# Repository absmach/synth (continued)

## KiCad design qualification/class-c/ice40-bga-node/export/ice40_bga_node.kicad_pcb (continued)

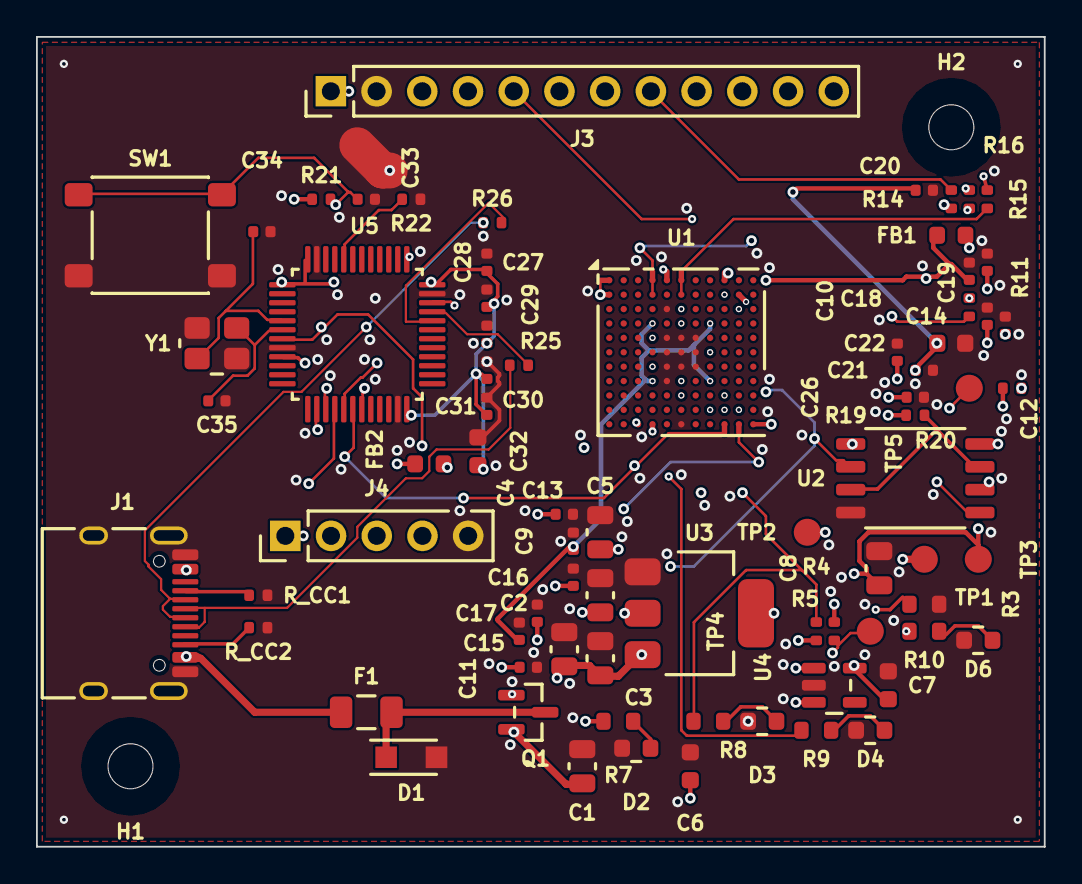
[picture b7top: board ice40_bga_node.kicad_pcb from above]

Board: 6 copper layers, 56.0 x 45.0 mm, 77 parts (0 on the bottom side), 42 nets.

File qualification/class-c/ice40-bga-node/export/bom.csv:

refdes,value,kind,description,kicad_symbol,kicad_footprint,lcsc_pn,mpn
C1,10uF,capacitor,"Generic 0805 MLCC, X7R/X5R, any value",Device:C,Capacitor_SMD:C_0805_2012Metric,,
C10,100nF,capacitor,"Generic 0402 MLCC, X7R/X5R, any value",Device:C,Capacitor_SMD:C_0402_1005Metric,,
C11,100nF,capacitor,"Generic 0402 MLCC, X7R/X5R, any value",Device:C,Capacitor_SMD:C_0402_1005Metric,,
C12,100nF,capacitor,"Generic 0402 MLCC, X7R/X5R, any value",Device:C,Capacitor_SMD:C_0402_1005Metric,,
C13,100nF,capacitor,"Generic 0402 MLCC, X7R/X5R, any value",Device:C,Capacitor_SMD:C_0402_1005Metric,,
C14,100nF,capacitor,"Generic 0402 MLCC, X7R/X5R, any value",Device:C,Capacitor_SMD:C_0402_1005Metric,,
C15,100nF,capacitor,"Generic 0402 MLCC, X7R/X5R, any value",Device:C,Capacitor_SMD:C_0402_1005Metric,,
C16,100nF,capacitor,"Generic 0402 MLCC, X7R/X5R, any value",Device:C,Capacitor_SMD:C_0402_1005Metric,,
C17,100nF,capacitor,"Generic 0402 MLCC, X7R/X5R, any value",Device:C,Capacitor_SMD:C_0402_1005Metric,,
C18,100nF,capacitor,"Generic 0402 MLCC, X7R/X5R, any value",Device:C,Capacitor_SMD:C_0402_1005Metric,,
C19,100nF,capacitor,"Generic 0402 MLCC, X7R/X5R, any value",Device:C,Capacitor_SMD:C_0402_1005Metric,,
C2,10uF,capacitor,"Generic 0805 MLCC, X7R/X5R, any value",Device:C,Capacitor_SMD:C_0805_2012Metric,,
C20,100nF,capacitor,"Generic 0402 MLCC, X7R/X5R, any value",Device:C,Capacitor_SMD:C_0402_1005Metric,,
C21,100nF,capacitor,"Generic 0402 MLCC, X7R/X5R, any value",Device:C,Capacitor_SMD:C_0402_1005Metric,,
C22,1uF,capacitor,"Generic 0603 MLCC, X7R/X5R, any value",Device:C,Capacitor_SMD:C_0603_1608Metric,,
C26,100nF,capacitor,"Generic 0402 MLCC, X7R/X5R, any value",Device:C,Capacitor_SMD:C_0402_1005Metric,,
C3,10uF,capacitor,"Generic 0805 MLCC, X7R/X5R, any value",Device:C,Capacitor_SMD:C_0805_2012Metric,,
C4,10uF,capacitor,"Generic 0805 MLCC, X7R/X5R, any value",Device:C,Capacitor_SMD:C_0805_2012Metric,,
C5,10uF,capacitor,"Generic 0805 MLCC, X7R/X5R, any value",Device:C,Capacitor_SMD:C_0805_2012Metric,,
C6,1uF,capacitor,"Generic 0603 MLCC, X7R/X5R, any value",Device:C,Capacitor_SMD:C_0603_1608Metric,,
C7,1uF,capacitor,"Generic 0603 MLCC, X7R/X5R, any value",Device:C,Capacitor_SMD:C_0603_1608Metric,,
C8,4.7uF,capacitor,"Generic 0805 MLCC, X7R/X5R, any value",Device:C,Capacitor_SMD:C_0805_2012Metric,,
C9,100nF,capacitor,"Generic 0402 MLCC, X7R/X5R, any value",Device:C,Capacitor_SMD:C_0402_1005Metric,,
D1,PTVS6V0S1UR,diode,"Nexperia PTVS6V0S1UR 400 W unidirectional TVS, 6.0 V standoff, SOD123W, for VBUS and CC",Device:D_Zener,Diode_SMD:Nexperia_CFP3_SOD-123W,,PTVS6V0S1UR
D2,0603-GREEN,led,"Green LED, 0603 package, ~2.2V Vf",Device:LED,LED_SMD:LED_0603_1608Metric,C72043,0603-GREEN
D3,(no value),led,"Amber surface-mount LED, 0603",Device:LED,LED_SMD:LED_0603_1608Metric,,
D4,0603-RED,led,"Red LED, 0603 package, ~2.0V Vf",Device:LED,LED_SMD:LED_0603_1608Metric,C2286,0603-RED
D6,0603-RED,led,"Red LED, 0603 package, ~2.0V Vf",Device:LED,LED_SMD:LED_0603_1608Metric,C2286,0603-RED
F1,MF-NSMF050-2,fuse,"Bourns MF-NSMF050-2 resettable fuse, 0.5 A hold, 13.2 V, 1206",Device:Polyfuse,Fuse:Fuse_1206_3216Metric,C75464,MF-NSMF050-2
FB1,(no value),inductor,"0603 ferrite bead, 600Ω @ 100MHz — EMI suppression",Device:FerriteBead,Inductor_SMD:L_0603_1608Metric,,
H1,(no value),mounting_hole,M2.5 non-plated mounting hole (NPTH) for a board corner,Mechanical:MountingHole,MountingHole:MountingHole_2.5mm,,
H2,(no value),mounting_hole,M2.5 non-plated mounting hole (NPTH) for a board corner,Mechanical:MountingHole,MountingHole:MountingHole_2.5mm,,
J1,HX PZ2.54-1x2P ZZ,connector,"1x2 through-hole pin header, 2.54mm pitch, for a jumper",Connector_Generic:Conn_01x02,Connector_PinHeader_2.54mm:PinHeader_1x02_P2.54mm_Vertical,C32713268,HX PZ2.54-1x2P ZZ
J3,(no value),connector,"1x12 through-hole pin header, 2.54 mm pitch (GPIO); datasheet_url is the product page of the Harwin M20 series, no manufacturer PDF link was verifiable",Connector_Generic:Conn_01x12,Connector_PinHeader_2.54mm:PinHeader_1x12_P2.54mm_Vertical,,
Q1,SI2301CDS-T1-GE3,transistor,"Vishay Si2301 P-channel power MOSFET, SOT-23",Transistor_FET:Si2301CDS,Package_TO_SOT_SMD:SOT-23,C10487,SI2301CDS-T1-GE3
R10,1k,resistor,"Generic 0603 thick-film resistor, any value",Device:R_US,Resistor_SMD:R_0603_1608Metric,,
R11,100,resistor,"Generic 0402 thick-film resistor, any value",Device:R_US,Resistor_SMD:R_0402_1005Metric,,
R14,100,resistor,"Generic 0402 thick-film resistor, any value",Device:R_US,Resistor_SMD:R_0402_1005Metric,,
R15,100,resistor,"Generic 0402 thick-film resistor, any value",Device:R_US,Resistor_SMD:R_0402_1005Metric,,
R16,100,resistor,"Generic 0402 thick-film resistor, any value",Device:R_US,Resistor_SMD:R_0402_1005Metric,,
R19,10k,resistor,"Generic 0402 thick-film resistor, any value",Device:R_US,Resistor_SMD:R_0402_1005Metric,,
R20,10k,resistor,"Generic 0402 thick-film resistor, any value",Device:R_US,Resistor_SMD:R_0402_1005Metric,,
R3,100k,resistor,"Generic 0603 thick-film resistor, any value",Device:R_US,Resistor_SMD:R_0603_1608Metric,,
R4,10k,resistor,"Generic 0402 thick-film resistor, any value",Device:R_US,Resistor_SMD:R_0402_1005Metric,,
R5,10k,resistor,"Generic 0402 thick-film resistor, any value",Device:R_US,Resistor_SMD:R_0402_1005Metric,,
R7,1k,resistor,"Generic 0603 thick-film resistor, any value",Device:R_US,Resistor_SMD:R_0603_1608Metric,,
R8,1k,resistor,"Generic 0603 thick-film resistor, any value",Device:R_US,Resistor_SMD:R_0603_1608Metric,,
R9,1k,resistor,"Generic 0603 thick-film resistor, any value",Device:R_US,Resistor_SMD:R_0603_1608Metric,,
TP1,(no value),testpoint,"SMD test point pad, 1.5 mm — probe point for a net",Connector:TestPoint,TestPoint:TestPoint_Pad_D1.5mm,,
TP2,(no value),testpoint,"SMD test point pad, 1.5 mm — probe point for a net",Connector:TestPoint,TestPoint:TestPoint_Pad_D1.5mm,,
TP3,(no value),testpoint,"SMD test point pad, 1.5 mm — probe point for a net",Connector:TestPoint,TestPoint:TestPoint_Pad_D1.5mm,,
TP4,(no value),testpoint,"SMD test point pad, 1.5 mm — probe point for a net",Connector:TestPoint,TestPoint:TestPoint_Pad_D1.5mm,,
TP5,(no value),testpoint,"SMD test point pad, 1.5 mm — probe point for a net",Connector:TestPoint,TestPoint:TestPoint_Pad_D1.5mm,,
U1,ICE40HX4K-BG121,fpga,"Lattice iCE40 HX4K FPGA, 121-ball 0.8mm BGA. Copy of registry part ice40hx4k_bg121 with exactly one change: vpp_fast (B10) is a passive pin that is not required, so it can be left unconnected.",FPGA_Lattice:ICE40HX4K-BG121,Package_BGA:BGA-121_9.0x9.0mm_Layout11x11_P0.8mm_Ball0.4mm_Pad0.35mm_NSMD,,ICE40HX4K-BG121
U2,W25Q128JVSIQ,memory,"Winbond W25Q128JVSIQ 128Mbit SPI NOR flash, SOIC-8 208 mil (5.3 mm body, 7.7 mm lead span, 1.27 mm pitch)",Memory_Flash:W25Q128JVS,Package_SO:SOIC-8_5.3x5.3mm_P1.27mm,C97521,W25Q128JVSIQ
U3,AMS1117-3.3,regulator,"AMS1117-3.3 fixed 3.3V LDO regulator, SOT-223 — common JLC stock",Regulator_Linear:AMS1117-3.3,Package_TO_SOT_SMD:SOT-223-3_TabPin2,C6186,AMS1117-3.3
U4,TLV70012-1.2,regulator,"TI TLV70012 1.2 V fixed LDO, 200 mA, 2.0 to 5.5 V input, SOT-23-THIN (DDC, TSOT-23-5). Pinout 1 IN, 2 GND, 3 EN, 4 NC, 5 OUT per TI TLV700xx datasheet SLVSA00; 1 uF input and output capacitors.",Regulator_Linear:TLV70012_SOT23-5,Package_TO_SOT_SMD:TSOT-23-5,,TLV70012DDCR

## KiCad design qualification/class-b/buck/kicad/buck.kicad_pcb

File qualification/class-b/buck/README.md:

# 24 V in, 3.3 V out buck with input parts (PTC, reverse-block diode, TVS) (SYN-67)

Status: designed, placed by a hand-pinned sidecar, routed, DRC and ERC counted, Gerber and drill files
generated. Not fabricated, not powered, no hardware test. Every part on the board that carries a
registry review record is signed; the last two, `lmr38010` and `ltst_c190kgkt`, were reviewed by Steve Munene
on 2026-10-29 and their review records are below. The fab package reports `release_ready: true`, which covers
Synth's routing and export gates only, not fabrication.
Intended for 24 V +10% in and 1 A out. The converter is rated 1 A, and the PTC and the input connector are
further limits (see Limits). No surge test was run. The TVS clamp (48.4 V at 12.4 A) is below the
converter's 85 V absolute maximum; a sustained overvoltage is limited by the PTC and the 50 V capacitors.

## Purpose

Ticket #67 under #38 (Class B qualification): a switching-regulator board with input and output filtering,
feedback, power-good and thermal copper, plus a negative variant that the feedback-safety rule
(E-SYNTH-POWER-011, PR #56) must flag.

## What

- `buck.synth`, negative `buck_neg_fb_sw.synth`, the placement sidecar `buck.placement.layout.toml`, hashes in `SHA256SUMS`, matrix and `#38` traceability in `QUALIFICATION.md`, evidence in `kicad/`, `reports/`, `images/`. `kicad/buck.step` is the board STEP with 3D models (`kicad-cli pcb export step --no-dnp`); the 3D views use the same stock KiCad models. The mounting holes have no model (the KiCad MountingHole step files are not installed).
- `kicad/`: the KiCad project, BOM, pick-and-place, `gerbers/` (22 Gerbers plus the job file, 4 copper layers) and `drill/` (PTH and NPTH). `reports/`: `release.json` (source/DRC gate) and `release-fab.json` (fab package), DRC, ERC, routing and connectivity.
- Chain: J1 (JST XH) -> F1 PTC -> D1 SS36 Schottky (reverse block) -> VIN node.
  VIN node: D2 SMBJ30A TVS, C1 47 uF bulk, C2 10 uF, C3 220 nF (on the U1 VIN pin), U1 LMR38010, UVLO divider.
- U1 -> L1 6.8 uH -> C5, C6, C9 (3x 22 uF, 25 V X7R) -> J2. C4 100 nF boot. R_RT 33k from RT/SYNC to GND sets 800 kHz. U1 has no VCC pin, so there is no VCC capacitor.
- U1 pins: 1 GND, 2 EN, 3 VIN, 4 RT/SYNC, 5 FB, 6 PG, 7 BOOT, 8 SW, 9 exposed pad.
- Feedback: R_FB_T 100k from the output node (L1 pad 2 side), R_FB_B 43.2k, C7 56 pF across R_FB_T.
  Vout = 1.0 x (1 + 100k/43.2k) = 3.315 V typical, 3.26 to 3.36 V over Vref 0.985 to 1.015 V (ideal resistors).
- Power-good: U1 pin 6 is open drain, pulled up to +3V3 through R_PG 100k and brought out on J2 pin 3. D4 (green, "PG FAULT") and R_PGLED 470 R run from +3V3 to PG, so the LED lights while PG is low and stays dark while power is good.
- Thermal: U1 pin 9 is a 2.41 x 3.1 mm exposed pad soldered to the F.Cu GND pour, with a 2 x 3 array of six GND vias in the pad (see Thermal). The board is `manufacturer "jlc-filled-via"` with `requires via_in_pad` (resin-filled and capped vias).
- Negative file: identical except R_FB_T and C7 hang from SW. It emits E-SYNTH-POWER-011 and the same 11 warnings as the good board.
- Board: 70.99 x 33.99 mm (2413 mm2, Edge.Cuts line centres), 4 layers, GND pours on all layers. Power tracks 0.5 mm, signal 0.127 mm.
- Two M2.5 non-plated mounting holes (H1, H2) in opposite corners.

## Why LMR38010 and not LMR33640

The first revision used the LMR33640 (38 V absolute maximum). A review found that the SMBJ30A clamps at 48.4 V
(12.4 A), above that maximum, so the TVS could not protect it. The LMR38010 is rated 85 V absolute maximum
(SW 85 V too), above the clamp. The change also removed the VCC pin and its capacitor, moved PG to pin 6
and VIN to pin 3, and added R_RT.

## UVLO (LMR38010 SNVSBM3B, 9.2.2.8, Eq 13 and 14)

Datasheet values: VEN-H (rising) 1.1 / 1.25 / 1.4 V and VEN-L (falling) 0.95 / 1.10 / 1.22 V (min/typ/max).
R_UV_B = 100k, R_UV_T = 1.37M, ratio 1 + 13.7 = 14.7.
- Start = 1.25 x 14.7 = 18.4 V typical (16.2 to 20.6 V over the VEN-H range).
- Stop = 1.10 x 14.7 = 16.2 V typical (14.0 to 17.9 V over the VEN-L range).
- The min and max of the two ranges are not independent, so the extreme pairs are not a guaranteed hysteresis. 1% resistors add about 1% to each figure.
- EN at 28 V in is 28 x 0.1/1.47 = 1.90 V; the EN absolute maximum is VIN + 0.3 V.

## Frequency and inductor

- R_RT 33k gives 800 kHz (datasheet RT versus frequency table under Figure 8-4; Table 8-1 lists 750 kHz at 34.8k and 1000 kHz at 25.5k). The RT/SYNC pin must not float (8.3.4).
- L1 6.8 uH: ripple (26.4 - 3.3) x (3.3/26.4) / (6.8 uH x 800 kHz) = 0.53 A pp at 26.4 V in. Eq 11 minimum is 0.25 x 3.3 / 800 kHz = 1.03 uH. At 1 A out the peak is about 1.27 A against Isat 5.7 A.
- Datasheet Table 9-1 has no 3.3 V row. Its 5 V rows use 2 to 3 x 22 uF; C5, C6 and C9 are 3 x 22 uF at 25 V X7R. DC-bias derating at 3.3 V is unknown and stability is unverified.

## Power-good

| Item | Value | Source |
| --- | --- | --- |
| Pin | U1 pin 6, open-drain NMOS | SNVSBM3B 8.3.5 |
| Pull-up | R_PG 100k to +3V3 | 8.3.5 allows a 100k pull-up to VOUT; the pin tolerates 20 V (7.1, 7.3) |
| Sink current | 33 uA through 100k, limit 5 mA DC | 8.3.5 |
| On-resistance | 92 ohm typ at VEN 3.3 V, 140 ohm at VEN 0 | 7.5 |
| Asserted low | during start-up, current limit and thermal shutdown, and when EN is low | 8.3.5 |
| Thresholds | rising 110 / 112 / 114 %, falling 90 / 92 / 94 % of VFB, hysteresis 2.2 % | 7.5 |
| Start-up delay | about 4 ms from EN asserted | 8.3.5 |
| Glitch filter | 40 us typ | 7.5 |
| Presented on | J2 pin 3 (3.3 V logic) | this board |

The netlist proves the connection (A15 in `QUALIFICATION.md`). Nothing proves the thresholds, the delay or
the behaviour on a fault: Synth has no power-good rule (`synth capability list` marks
`power_sequencing_and_power_good` unsupported), and this board was not powered.

## Thermal

- U1's exposed pad (pin 9, 2.41 x 3.1 mm, centre (33.0, 16.0) mm) is soldered to the F.Cu GND pour and holds
  a 2 x 3 array of six GND vias (0.6 mm pad, 0.3 mm drill, 1.2 mm apart), declared in
  `buck.placement.layout.toml` as `[[vias]]`. The PCB export writes them before routing, so the router
  treats them as GND copper. TI asks for at least a 4 x 3 array of 10 mil vias (9.5.1.1); six vias is fewer.
- Via-in-pad needs resin-filled and capped vias, so the board declares `manufacturer "jlc-filled-via"` and
  `requires via_in_pad`; `release.json` lists the six vias as fabrication notes.
- Counts from `kicad/buck.kicad_pcb` (`vias.py`, GND vias, distance from the pad centre): inside the pad 6;
  within 1 mm 2, within 2 mm 6, within 3 mm 6, within 4 mm 7. The board has 21 vias in total, all GND, all
  0.3 mm drill and 0.6 mm pad. The other 15 were placed by the router.
- Not estimated: TI's `RthetaJA` of 42.9 C/W is not valid for design (datasheet text near Eq 15), the LMR38010
  datasheet has no copper-area curve, and no efficiency curve was read. At 1 A out and an assumed 85% efficiency the loss
  would be 3.3/0.85 - 3.3 = 0.58 W; the junction temperature is left to the expert (B2).

## Parts and datasheets (read 2026-10-24 and 2026-10-29)

| Part | Datasheet | Revision | Values taken | Conflict or gap |
| --- | --- | --- | --- | --- |
| U1 TI LMR38010SDDAR (HSOIC-8 DDA) | https://www.ti.com/lit/ds/symlink/lmr38010.pdf | SNVSBM3B | 4.2-80 V recommended, 85 V abs max (SW 85 V); 1 A; 200-2200 kHz adjustable; internal compensation; VREF 1.0 V (0.985-1.015); EN rising 1.1/1.25/1.4 V, falling 0.95/1.10/1.22 V; PG tolerates 20 V; pins 1 GND, 2 EN, 3 VIN, 4 RT/SYNC, 5 FB, 6 PG, 7 BOOT, 8 SW, 9 EP; Cin at least 4.7 uF plus 100-220 nF (9.2.2.6) | Table 8-1 has no 800 kHz row; the RT table under Figure 8-4 gives 33k. Table 9-1 has no 3.3 V row |
| L1 Bourns SRN6045TA-6R8M | https://www.bourns.com/docs/Product-Datasheets/SRN6045TA.pdf | REV. 06/24 (footer) | 6.8 uH +-20%, DCR 34 mOhm typ, Irms 3.6 A, Isat 5.7 A (L -30%), 6.0 x 6.0 mm | Registry has no Isat field; Isat is in the description |
| D1 Vishay SS36 | https://www.vishay.com/docs/88751/ss32.pdf | 23-Apr-2020 (doc 88751) | VRRM 60 V, 3 A, IFSM 100 A, VF 0.75 V max at 3 A, IR 0.5 mA at 25 C and 10 mA at 100 C, SMC | Drawn with KiCad `Device:D_Schottky`; the footprint is `Diode_SMD:D_SMC`. VF at low current not read |
| D2 Vishay SMBJ30A | https://www.vishay.com/docs/88392/smbj.pdf | 09-Jan-2024 (doc 88392) | 600 W 10/1000 us, VWM 30 V, VBR 33.3-36.8 V at 1 mA, VC 48.4 V at 12.4 A, VBR temperature coefficient 0.099 %/C, SMB | No KiCad SMBJ30A symbol; Device:D_Zener used. Registry `max_voltage_v` 30 is VWM. The clamp is below U1's 85 V absolute maximum |
| F1 Bourns MF-MSMF110/33X | https://www.bourns.com/docs/Product-Datasheets/mfmsmf.pdf | REV. BE, 09/26 (footer) | Vmax 33 V, Imax 20 A, Ihold 1.1 A at 23 C, 0.93 A at 40 C, 0.73 A at 60 C, 0.63 A at 70 C, 0.50 A at 85 C, Itrip 2.2 A, R 0.06-0.20 Ohm | none found. Registry `max_current_ma` 1100 is Ihold at 23 C |
| J1, J2 JST B2B-XH-A / B4B-XH-A | https://www.jst-mfg.com/product/pdf/eng/eXH.pdf | none printed | 2.5 mm pitch, 3 A, 250 V | Existing registry `jst_xh_2pin`/`jst_xh_4pin` say 5 V / 100 mA; that conflicts with this sheet, so new parts were added |
| D3, D4 Lite-On LTST-C190KGKT | https://optoelectronics.liteon.com/upload/download/DS22-2000-074/LTST-C190KGKT.PDF | Spec No. DS22-2000-074, Revision O, effective 09/04/2021 (read 2026-10-29) | see the review record below | none against the registry file; one footprint difference, below |
| C1 47 uF | Honor Elec RVT1H470M0810 (JLCPCB C2895739) | [LCSC datasheet](https://wmsc.lcsc.com/wmsc/upload/file/pdf/v2/lcsc/2109290630_Honor-Elec-RVT1H470M0810_C2895739.pdf) | 47 uF, 50 V, +/-20 %, 105 C, 8 x 10.2 mm SMD; ripple 120 mA at 120 Hz | ESR not given |
| C2, C5, C6, C9 (1206), C3, C4, C7, R_RT and the other resistors (0603) | none | | generic registry parts; voltage and dielectric are set per instance in `buck.synth` | no MPN. Murata and TDK pages returned 404/403/500: no DC-bias data |

### Review record: D3, D4 Lite-On LTST-C190KGKT

Read from the datasheet above on 2026-10-29. Registry file `registry/parts/diodes/ltst_c190kgkt.synth.toml`.

- Package: 1.6 x 0.8 mm body, 0.8 mm tall, 0.4 mm terminals, cathode marked on the package. Recommended pad 0.8 x 0.8 mm each, 2.3 mm outer span.
- Ratings: DC forward current 30 mA, power 75 mW, reverse voltage 5 V. Electrical: VF 1.9-2.4 V at 20 mA, IV 18-71 mcd at 20 mA, dominant wavelength 567.5-576.5 nm (green AlInGaP), IR 10 uA at 5 V.
- Registry: pin 1 cathode, pin 2 anode; `kicad_symbol` Device:LED (K=1, A=2); footprint `LED_SMD:LED_0603_1608Metric` (pad 1 cathode, pad 2 anode); `max_current_ma` 30 agrees with the DC rating; Vf 1.9 to 2.4 V in the description agrees; width 2.96 mm is the footprint courtyard width, not a datasheet figure.
- Footprint: the KiCad pads are 0.875 x 0.95 mm at +-0.7875 mm, an outer span of 2.45 mm. Datasheet: 0.8 x 0.8 mm and 2.3 mm. So the KiCad pads are 0.075 mm wider, 0.15 mm longer in Y, and the outer span is 0.15 mm larger. Polarity agrees. Pad shape differences are for the reviewer to accept.
- Circuit: D3 from +3V3 through R_LED 470 ohm: (3.3 - 2.4 to 1.9) / 470 = 1.9 to 3.0 mA, well under 30 mA. D4 likewise through R_PGLED.
- Not checked: availability, LCSC number, the Lite-On temperature derating curve against the board temperature.

Reviewed by Steve Munene on 2026-10-29; `reviewed_by` and `reviewed_at` are set in the registry file.

### Review record: U1 TI LMR38010SDDAR

Read from SNVSBM3B (text copy), 2026-10-29. Registry file `registry/parts/regulators/lmr38010.synth.toml`.

- Pins: registry gnd 1, en 2, vin 3, rt_sync 4, fb 5, pg 6, boot 7, sw 8, pad 9; the datasheet pin table agrees.
- Ratings used: operating 4.2 to 80 V (registry min 4.2, max 80, 1000 mA); absolute maximum VIN and SW 85 V, EN VIN + 0.3 V, FB and RT/SYNC 5.5 V, PG 20 V; VREF 1.0 V; junction temperature -40 to 150 C.
- Footprint: `HSOP-8-1EP_3.9x4.9mm_P1.27mm_EP2.41x3.1mm`, exposed pad 2.41 x 3.1 mm. The datasheet DDA land pattern shows a 2.40 x 3.10 mm pad. The 0.01 mm difference is below the drawing tolerance. The signal pads are 1.6 x 0.6 mm on a 1.27 mm pitch; they were not compared with the DDA drawing line by line.
- Application: Cin at least 4.7 uF plus 100-220 nF (C2 10 uF, C3 220 nF); inductor above the Eq 11 minimum (1.03 uH against 6.8 uH); PG pull-up and EN divider as in the sections above.
- Not checked: availability, LCSC number.

Reviewed by Steve Munene on 2026-10-29; `reviewed_by` and `reviewed_at` are set in the registry file.

## Limits and honesty notes

- Overvoltage: the converter is rated 80 V operating and 85 V absolute maximum. SMBJ30A has VBR 33.3 to 36.8 V
  and VC 48.4 V at 12.4 A (Vishay smbj.pdf, 600 W 10/1000 us), below the 85 V maximum, so a surge the TVS can
  absorb leaves the regulator inside its absolute maximum. A SUSTAINED overvoltage is limited by other parts:
  the PTC F1 (Vmax 33 V) and the 50 V ratings of C1, C2 and C3. No surge test was run and no IEC 61000-4-5
  rating is claimed. The TVS energy, the PTC under surge and the capacitors at the 48.4 V clamp (50 V parts,
  1.6 V margin) are for the expert (B1). The TVS standoff (30 V) is above the 26.4 V maximum input, so it
  does not conduct on a healthy rail.
- PTC and rating: output current is rated 1 A (the converter's limit). At 1 A out the input current is
  3.3 / 0.85 / 24 = 0.162 A at 24 V and 0.240 A at the UVLO stop voltage (16.2 V), against F1 Ihold 0.63 A at
  70 C (3.9x and 2.6x). The 85% efficiency is an assumption.
- Output capacitors: C5, C6 and C9 are 22 uF 25 V X7R 1206. DC-bias derating at 3.3 V is unknown. The internal
  compensation is specified for a range of inductance and capacitance; stability is unverified.
- Input capacitors: the datasheet asks for at least 4.7 uF plus 100-220 nF. C2 is 10 uF X7R 50 V; its effective
  value at 24 V is unknown. C1 47 uF electrolytic adds bulk with unknown ESR.
- Reverse polarity: Schottky chosen over a P-FET. SS36 VRRM 60 V against 26 V. Drop 0.75 V max at 3 A,
  so under 0.13 W at 0.162 A (bound; VF at low current not read). A P-FET at 24 V needs a gate clamp;
  no P-FET datasheet was read.

## Commands

```
export XDG_DATA_HOME=$(mktemp -d)   # empty dir: a user overlay in ~/.local/share/synth shadows registry parts
export KICAD_SYMBOL_DIR=/usr/share/kicad/symbols KICAD_FOOTPRINT_DIR=/usr/share/kicad/footprints
scripts/setup-routing-engines.sh --freerouting-only          # FreeRouting jar + Java, or symlink tools/freerouting and tools/jre25
B=qualification/class-b/buck                                 # relative to the repo root
synth validate $B/buck.synth
SYNTH_SOURCE_REVISION=$(git rev-parse HEAD) synth export-kicad $B/buck.synth --out out/buck \
  --allow-unverified-parts --validate-erc --router free-routing --pnp --gerbers --drill   # fab package: reports/release-fab.json
SYNTH_SOURCE_REVISION=$(git rev-parse HEAD) synth export-kicad $B/buck.synth --out out/buck-nofab \
  --allow-unverified-parts --validate-erc --router free-routing                           # source/DRC gate: reports/release.json
kicad-cli pcb drc --severity-all --refill-zones --format json -o $B/reports/buck.kicad-drc.json $B/kicad/buck.kicad_pcb
kicad-cli sch erc --severity-all --format json -o $B/reports/buck.kicad-erc.json $B/kicad/buck.kicad_sch
synth validate $B/buck_neg_fb_sw.synth
python3 -I $B/pad_gaps.py $B/kicad/buck.kicad_pcb
```

`out/` is gitignored scratch. The sidecar `buck.placement.layout.toml` decides placement; there is no
`--place-route-iterate`. The two `export-kicad` runs differ only in whether the fab gate is asked, which is why
there are two release reports. The repository root prefix was stripped from the JSON reports with `sed`.
Registry parts were authored or imported with `synth part import-kicad` and then edited by hand (names, MPN,
dimensions, datasheet URL, `switch_node` on SW and `feedback` on FB); `lmr38010` is hand-written from the
datasheet.

## Measured results

The export routes with FreeRouting 2.4.1 on OpenJDK 25.0.4.1; the routed board is written as `out/buck/buck.kicad_pcb` when Synth's gate passes (state `routed`). Numbers below are from the committed files, measured 2026-10-29. `reports/buck.routing.json` records `source_revision` a9c7546e4aeecee7719aa003f3699064bb30b912, the commit of the sources the board was built from.

| Number | Value | Command |
| --- | --- | --- |
| validate, good board | exit 0, 0 errors, 11 warnings (3 E-SYNTH-SCHEM-003, 1 E-SYNTH-SCHEM-004, 4 E-SYNTH-SCHEM-005, 1 W-SYNTH-ANOMALY-001, 2 W-SYNTH-SUPPLY-002) | `synth validate $B/buck.synth 2>&1 \| grep -o '^warning: \[[A-Z0-9-]*\]' \| sort \| uniq -c` |
| validate, negative | exit 1, 1 error (E-SYNTH-POWER-011), the same 11 warnings | same on `buck_neg_fb_sw.synth` |
| routing | `routed`, 13 nets connected, 0 open, 97 segments (all F.Cu), 21 vias, 200.08 mm | `reports/buck.routing.json` `statistics`; the PCB file also holds 97 segments and 21 vias |
| Synth routing check | kicad_drc 0 errors, 0 unconnected, 0 warnings | `reports/buck.routing.json` `validation` |
| Release gate | `release_ready` true, `production_status` production, 0 signal-integrity findings (0 `W-SYNTH-DRC-016`); with `--gerbers --drill` the same board also reports `release_ready` true and `production`, and its `reviewer_state` lists `lmr38010` and `ltst_c190kgkt` as reviewed (Steve Munene, 2026-10-29) | `reports/release.json`, `reports/release-fab.json` |
| DRC | 0 errors, 0 unconnected, 0 warnings | `kicad-cli pcb drc ... -o reports/buck.kicad-drc.json` |
| ERC | 0 violations | `kicad-cli sch erc ... -o reports/buck.kicad-erc.json` |
| Schematic netlist | 13 nets: the source's 7 `net` blocks plus the 6 further names its 10 `connect` statements create (`+3V3` joins an existing net), node for node | `kicad-cli sch export netlist --format kicadsexpr -o /tmp/buck.net $B/kicad/buck.kicad_sch` |
| Outline | 70.99 x 33.99 mm (x 0.55 to 71.54, y 0.55 to 34.54), 2413 mm2 | `grep -A3 gr_line $B/kicad/buck.kicad_pcb \| grep -E 'start\|end'` |
| Manufacturing exports | 22 Gerbers plus the job file (4 copper layers), PTH 27 holes (21 x 0.3 mm vias, 4 x 0.95 mm and 2 x 1.0 mm connector pins), NPTH 2 x 2.5 mm mounting holes | `ls $B/kicad/gerbers $B/kicad/drill`; `grep -c '^X' $B/kicad/drill/buck-PTH.drl` |
| Hashes | full values in `SHA256SUMS` and `QUALIFICATION.md` | `cd $B && grep -v '^#' SHA256SUMS \| sha256sum -c -` |

Pad-edge gaps in the placed, routed board, from `pad_gaps.py` (pcbnew pad bounding boxes, edge to edge):

| Pair | Gap mm |
| --- | --- |
| C3 (220 nF) to U1 VIN | 0.82 |
| C2 (10 uF) to U1 VIN | 1.46 |
| C3 / C2 ground pad to U1 GND | 2.69 / 5.35 |
| C4 to U1 BOOT / SW | 0.62 / 2.18 |
| R_RT to U1 RT/SYNC | 1.22 |
| L1 pad 1 to U1 SW | 3.80 |
| C5, C6, C9 to L1 pad 2 | 0.83 / 2.29 / 0.70 |
| D2 TVS to U1 VIN | 7.82 |
| R_UV_T to U1 EN | 3.35 |
| R_PG to U1 PG | 22.63 |
| R_FB_T / R_FB_B to U1 FB | 3.55 / 3.79 |
| C7 to R_FB_T (FB side) | 0.55 |
| R_FB_B ground pad to U1 GND | 11.31 |
| R_FB_T FB pad to L1 pad 1 (SW) | 2.58 |

## Placement

The placement is a hand-pinned layout in `buck.placement.layout.toml`: all 27 parts are pinned with hard
priority, plus two label offsets for R_FB_T and nothing else. Synth's unassisted auto placement was dropped
because it left C3 19.8 mm from VIN, the output capacitors 12.9 to 19.3 mm from L1 and 8 W-SYNTH-DRC-016
return-path warnings (a reviewer's finding). Choices:
- J1 -> F1 -> D1 sit below U1, so VIN does not cross the EN divider.
- C3 and C2 sit left of U1 at the VIN pad; C4 beside BOOT; R_RT beside RT/SYNC.
- C5, C6 and C9 form a short column right of L1.
- J2 is rotated 270 degrees so PG (pin 3) and +3V3 (pin 1) do not cross; R_PG and the PG LED chain sit beside J2.
- R_PG is 22.63 mm from the PG pin: the pull-up serves J2, and the PG track is a signal.

`pad_gaps.py` on the final routed file is the reference for gaps. The outline follows the pinned part
positions and the two corner holes; it is larger than the earlier auto placement of the LMR33640 version
(60.75 x 31.855 mm), and I did not isolate the cause of the 478 mm2 growth.

## Negative case: feedback from the switch node

`synth validate $B/buck_neg_fb_sw.synth` exits 1 (JSON, schema 1.3):
```
error: [E-SYNTH-POWER-011] regulator feedback is taken from the switching node
  found:    feedback pin `U1.fb` (group "FEEDBACK") is joined through resistor `R_FB_T` to switch-node pin `U1.sw` (group "BUCK")
  expected: the feedback pin to sense the regulated output, not the switching node
```
`synth export-kicad` stops with "Synth ERC validation failed; use --force to export anyway" (exit 2). The good board does not raise it. The rule follows one resistor only.

## Qualification matrix

The matrix (A: checked by tools, B: needs an expert) is in [`QUALIFICATION.md`](QUALIFICATION.md),
together with the `#38` checklist traceability for this board. Its row for the corpus is in
`qualification/matrix.toml` (section D there). Evidence files: `kicad/`, `reports/`, `images/`.

## Not true yet

- Not fabricable on this evidence: nothing was built and no surge test was run. The fab package's
  `release_ready: true` covers only Synth's routing and export gates (its `gate_scope`), not fabrication.
- Layout: current loop area, return-current paths and EMI were not analysed. The layer changes are the 21 GND
  vias; no signal net changes layer (all 97 segments are on F.Cu).
- Six thermal vias, where TI asks for at least 4 x 3 (9.5.1.1).
- Silkscreen: the "PG FAULT" and "PWR" LED values are on the F.Fab layer only, so the board prints just the references D4 and D3. Synth has no silk text for a value here. KiCad DRC reports no silkscreen violation.
- Schematic (rendered by `tools/schematic_quality.py`): 0 overlapping text pairs, 7 texts with a wire through them, 1 wire crossing, 1313.2 mm of wire; mean passive-to-pin distance 66.4 mm (max 172.8). No schematic sidecar is used.
- Routing used FreeRouting defaults, no length or coupling constraints.

## Not verified

- Nothing powered, measured or thermally tested. Efficiency (85%) and the 0.58 W loss are assumptions.
- The MCP placement review (`synth_describe_placement`) was not rerun on the hand-pinned placement.
- Availability, LCSC numbers and assembly not checked. Generic passives have no MPN or manufacturer sheet.
- PTC behaviour with the TVS in a surge, and inrush into C1 and the output caps, are not analysed.
- The Gerbers and drill files were not opened in a fab's DFM tool and no fab accepted them; the via-in-pad process was not confirmed with a fab.
- `synth check` on this board was not run to a verdict: it selects KiCadRoutingTools, which was not installed (the DRC stage reports `unknown`).
- Hash reproducibility on another machine depends on FreeRouting 2.4.1, the Java build and KiCad 10.0.7.

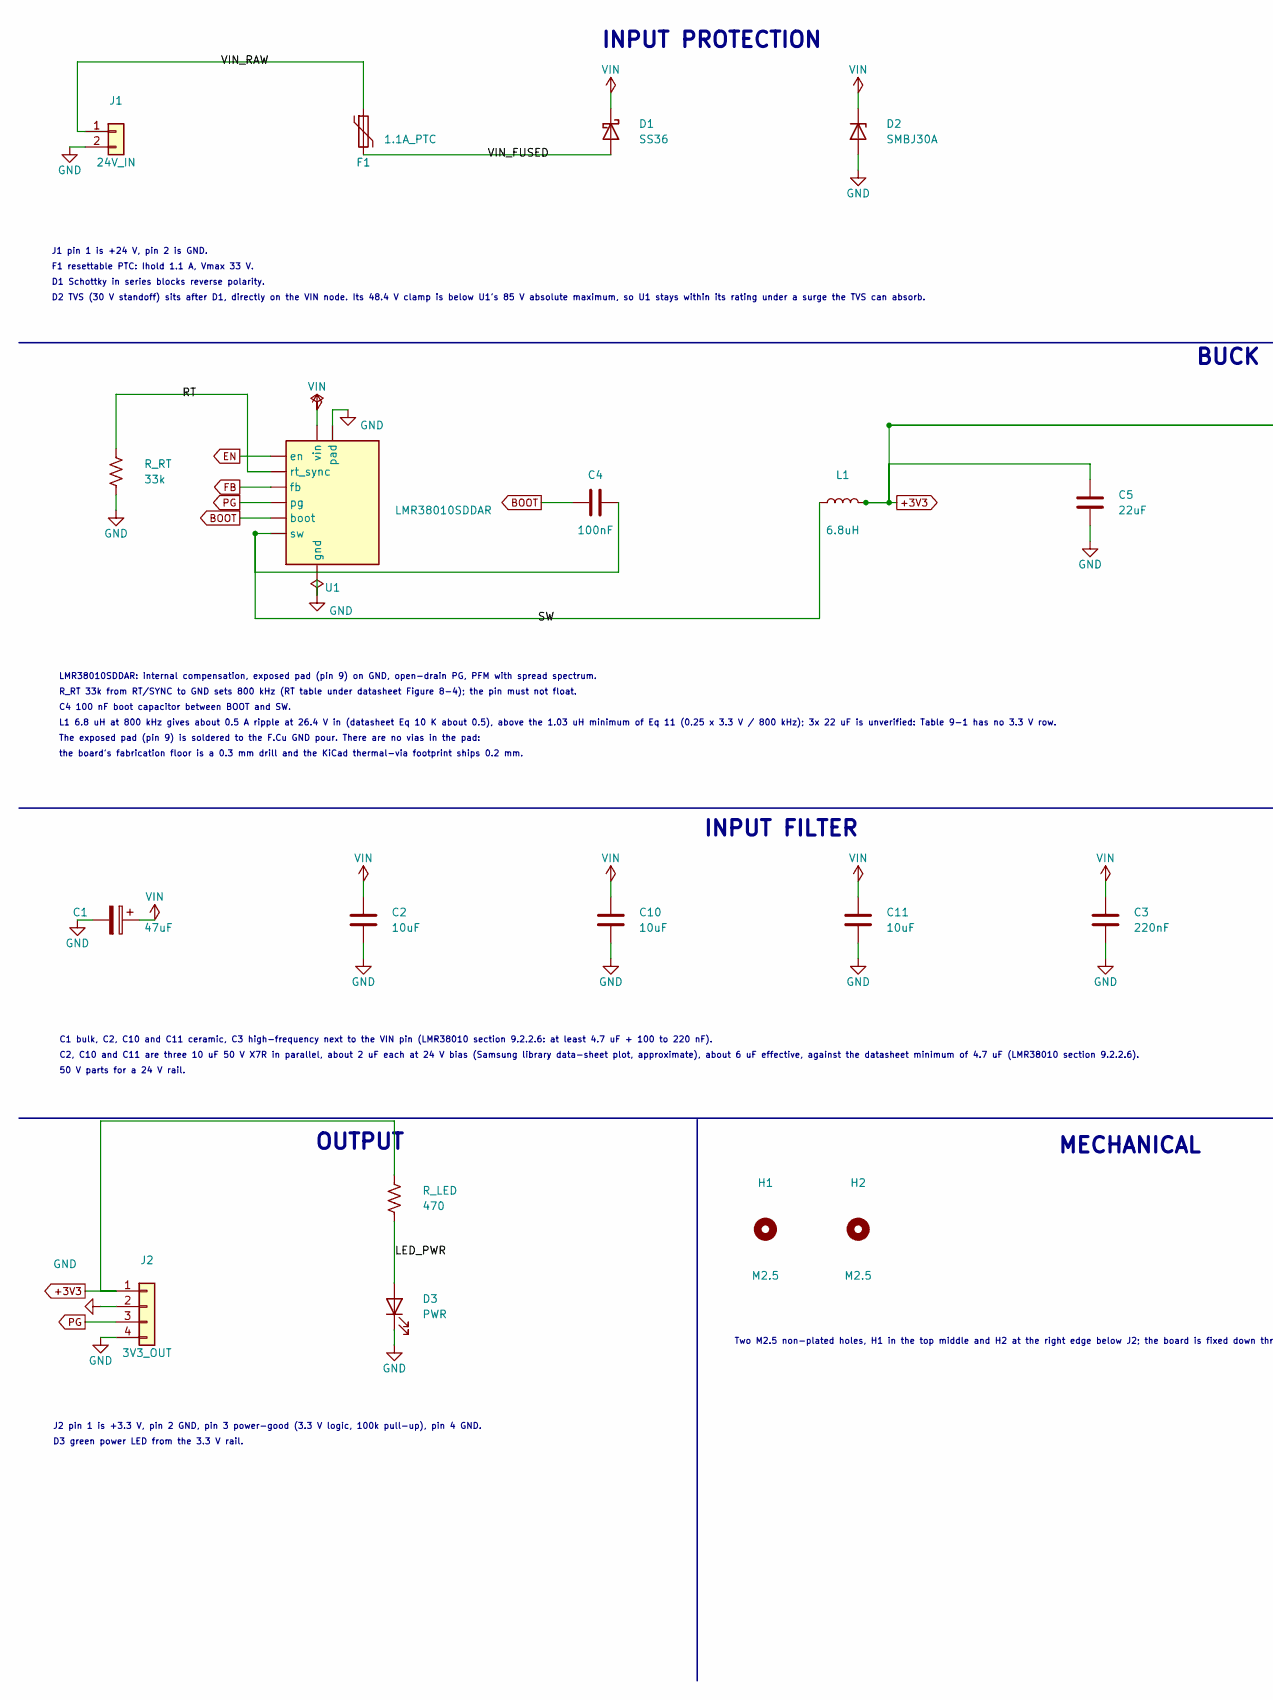
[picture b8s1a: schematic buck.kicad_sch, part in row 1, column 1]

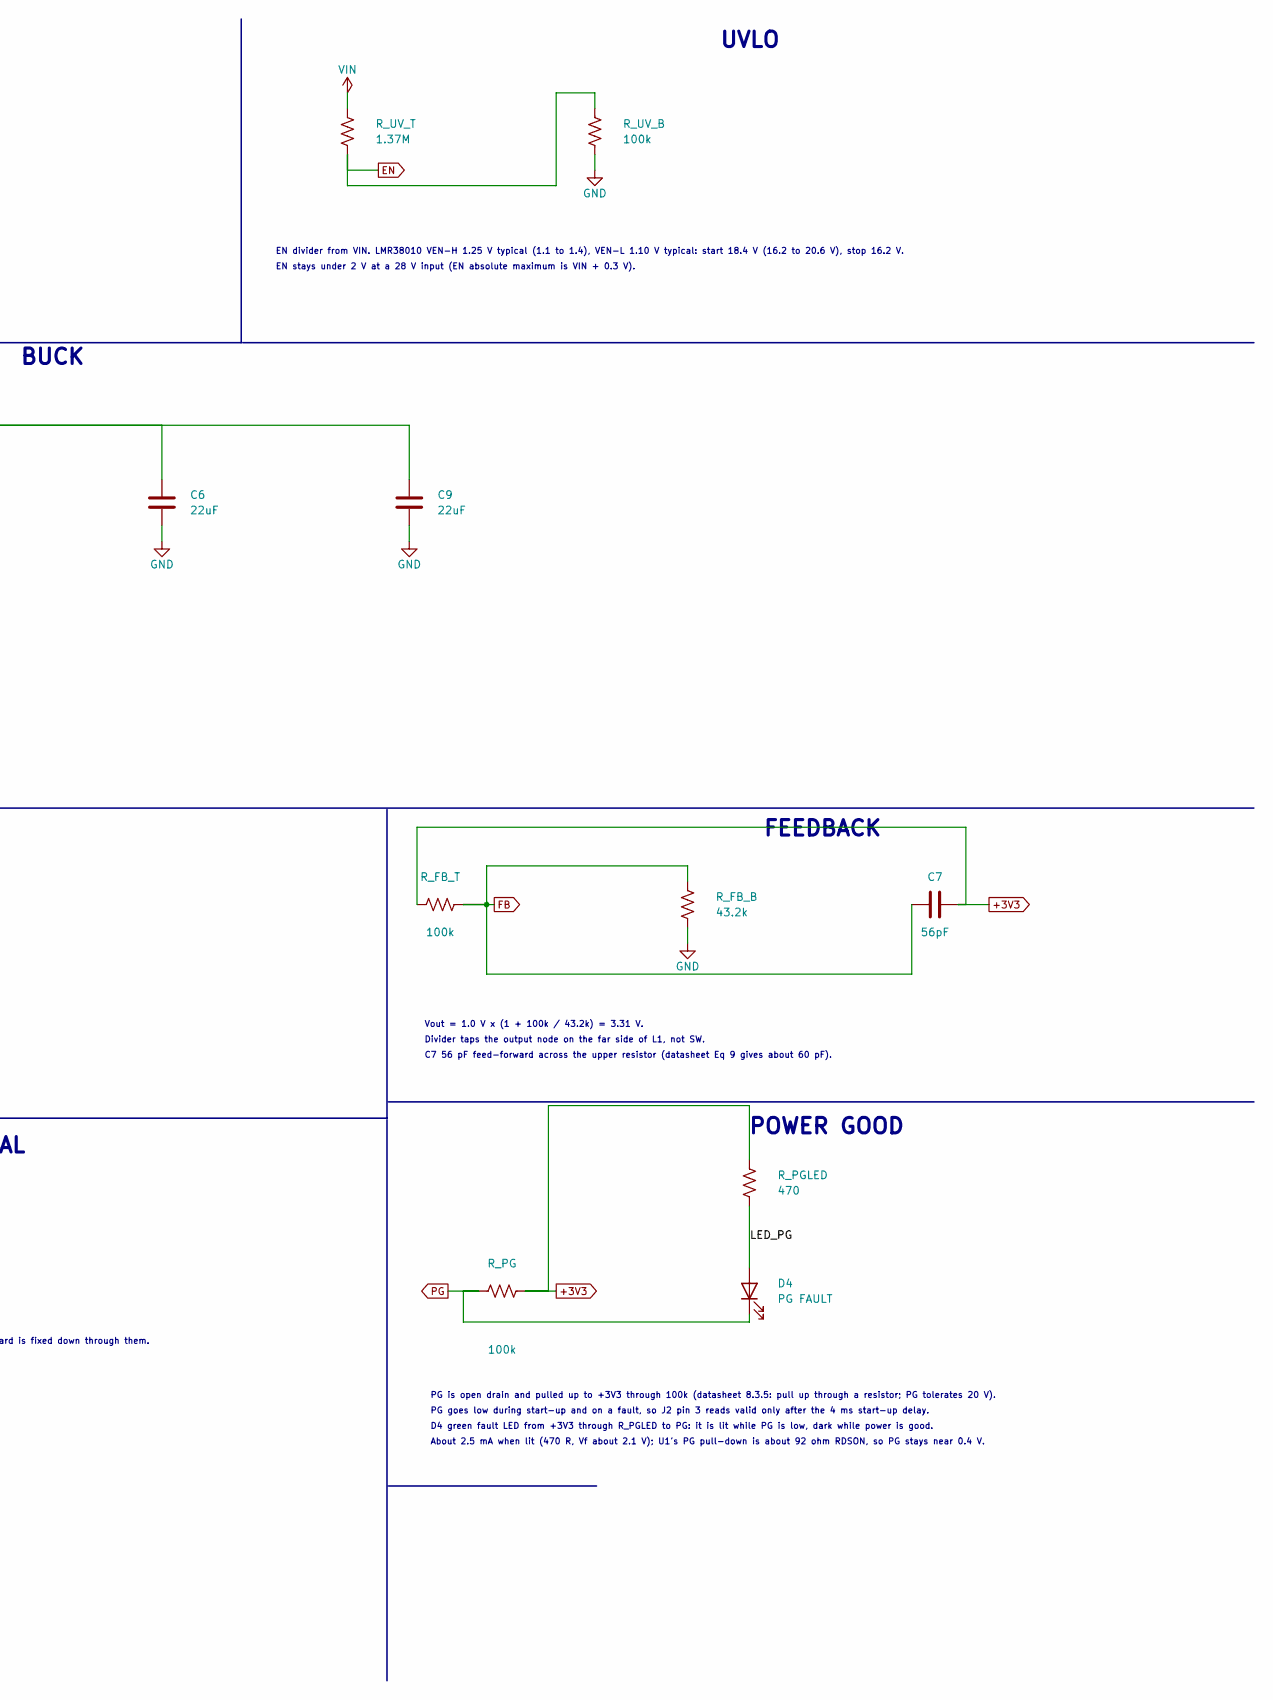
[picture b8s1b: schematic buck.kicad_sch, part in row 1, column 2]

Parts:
C1: 47uF; CP_Elec_8x10; Voltage 50V; MPN RVT1H470M0810
C2, C10, C11: 10uF; C_1206_3216Metric; Voltage 50V; MPN CL31B106KBHNNNE; LCSC C89632
C3: 220nF; C_0603_1608Metric; Voltage 50V
C4: 100nF; C_0603_1608Metric; Voltage 16V
C5, C6, C9: 22uF; C_1206_3216Metric; Voltage 25V; MPN CL31A226KAHNNNE; LCSC C12891
C7: 56pF; C_0603_1608Metric; Voltage 50V
D1: SS36; D_SMC; MPN SS36
D2: SMBJ30A; D_SMB; MPN SMBJ30A
D3: PWR; LED_0603_1608Metric; MPN LTST-C190KGKT
D4: PG FAULT; LED_0603_1608Metric; MPN LTST-C190KGKT
F1: 1.1A_PTC; Fuse_1812_4532Metric; MPN MF-MSMF110/33X
H1, H2: M2.5; MountingHole_2.5mm
J1: 24V_IN; JST_XH_B2B-XH-A_1x02_P2.50mm_Vertical; MPN B2B-XH-A
J2: 3V3_OUT; JST_XH_B4B-XH-A_1x04_P2.50mm_Vertical; MPN B4B-XH-A
L1: 6.8uH; L_Bourns_SRN6045TA; MPN SRN6045TA-6R8M
R_FB_B: 43.2k; R_0603_1608Metric; Tolerance 1%
R_FB_T: 100k; R_0603_1608Metric; Tolerance 1%
R_LED: 470; R_0603_1608Metric
R_PG: 100k; R_0603_1608Metric
R_PGLED: 470; R_0603_1608Metric
R_RT: 33k; R_0603_1608Metric; Tolerance 1%
R_UV_B: 100k; R_0603_1608Metric; Tolerance 1%
R_UV_T: 1.37M; R_0603_1608Metric; Tolerance 1%
U1: LMR38010SDDAR; HSOP-8-1EP_3.9x4.9mm_P1.27mm_EP2.41x3.1mm; MPN LMR38010SDDAR

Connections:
+3V3: C5.1, C6.1, C7.2, C9.1, J2.1, L1.2, R_FB_T.1, R_LED.1, R_PG.2, R_PGLED.1
BOOT: C4.1, U1.7 (boot)
EN: R_UV_B.1, R_UV_T.2, U1.2 (en)
FB: C7.1, R_FB_B.1, R_FB_T.2, U1.5 (fb)
GND: C1.2, C2.2, C3.2, C5.2, C6.2, C9.2, C10.2, C11.2, D2.2 (A), D3.1 (K), J1.2, J2.2, J2.4, R_FB_B.2, R_RT.2, R_UV_B.2, U1.1 (gnd), U1.9 (pad)
LED_PG: D4.2 (A), R_PGLED.2
LED_PWR: D3.2 (A), R_LED.2
PG: D4.1 (K), J2.3, R_PG.1, U1.6 (pg)
RT: R_RT.1, U1.4 (rt_sync)
SW: C4.2, L1.1, U1.8 (sw)
VIN: C1.1, C2.1, C3.1, C10.1, C11.1, D1.1 (K), D2.1 (K), R_UV_T.1, U1.3 (vin)
VIN_FUSED: D1.2 (A), F1.2
VIN_RAW: F1.1, J1.1

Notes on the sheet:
INPUT PROTECTION
INPUT FILTER
UVLO
BUCK
FEEDBACK
POWER GOOD
OUTPUT
MECHANICAL
J1 pin 1 is +24 V, pin 2 is GND.
F1 resettable PTC: Ihold 1.1 A, Vmax 33 V.
D1 Schottky in series blocks reverse polarity.
D2 TVS (30 V standoff) sits after D1, directly on the VIN node. Its 48.4 V clamp is below U1's 85 V absolute maximum, so U1 stays within its rating under a surge the TVS can absorb.
C1 bulk, C2, C10 and C11 ceramic, C3 high-frequency next to the VIN pin (LMR38010 section 9.2.2.6: at least 4.7 uF + 100 to 220 nF).
C2, C10 and C11 are three 10 uF 50 V X7R in parallel, about 2 uF each at 24 V bias (Samsung library data-sheet plot, approximate), about 6 uF effective, against the datasheet minimum of 4.7 uF (LMR38010 section 9.2.2.6).
50 V parts for a 24 V rail.
EN divider from VIN. LMR38010 VEN-H 1.25 V typical (1.1 to 1.4), VEN-L 1.10 V typical: start 18.4 V (16.2 to 20.6 V), stop 16.2 V.
EN stays under 2 V at a 28 V input (EN absolute maximum is VIN + 0.3 V).
LMR38010SDDAR: internal compensation, exposed pad (pin 9) on GND, open-drain PG, PFM with spread spectrum.
R_RT 33k from RT/SYNC to GND sets 800 kHz (RT table under datasheet Figure 8-4); the pin must not float.
C4 100 nF boot capacitor between BOOT and SW.
L1 6.8 uH at 800 kHz gives about 0.5 A ripple at 26.4 V in (datasheet Eq 10 K about 0.5), above the 1.03 uH minimum of Eq 11 (0.25 x 3.3 V / 800 kHz); 3x 22 uF is unverified: Table 9-1 has no 3.3 V row.
The exposed pad (pin 9) is soldered to the F.Cu GND pour. There are no vias in the pad:
the board's fabrication floor is a 0.3 mm drill and the KiCad thermal-via footprint ships 0.2 mm.
Vout = 1.0 V x (1 + 100k / 43.2k) = 3.31 V.
Divider taps the output node on the far side of L1, not SW.
C7 56 pF feed-forward across the upper resistor (datasheet Eq 9 gives about 60 pF).
PG is open drain and pulled up to +3V3 through 100k (datasheet 8.3.5: pull up through a resistor; PG tolerates 20 V).
PG goes low during start-up and on a fault, so J2 pin 3 reads valid only after the 4 ms start-up delay.
D4 green fault LED from +3V3 through R_PGLED to PG: it is lit while PG is low, dark while power is good.
About 2.5 mA when lit (470 R, Vf about 2.1 V); U1's PG pull-down is about 92 ohm RDSON, so PG stays near 0.4 V.
J2 pin 1 is +3.3 V, pin 2 GND, pin 3 power-good (3.3 V logic, 100k pull-up), pin 4 GND.
D3 green power LED from the 3.3 V rail.
Two M2.5 non-plated holes, H1 in the top middle and H2 at the right edge below J2; the board is fixed down through them.

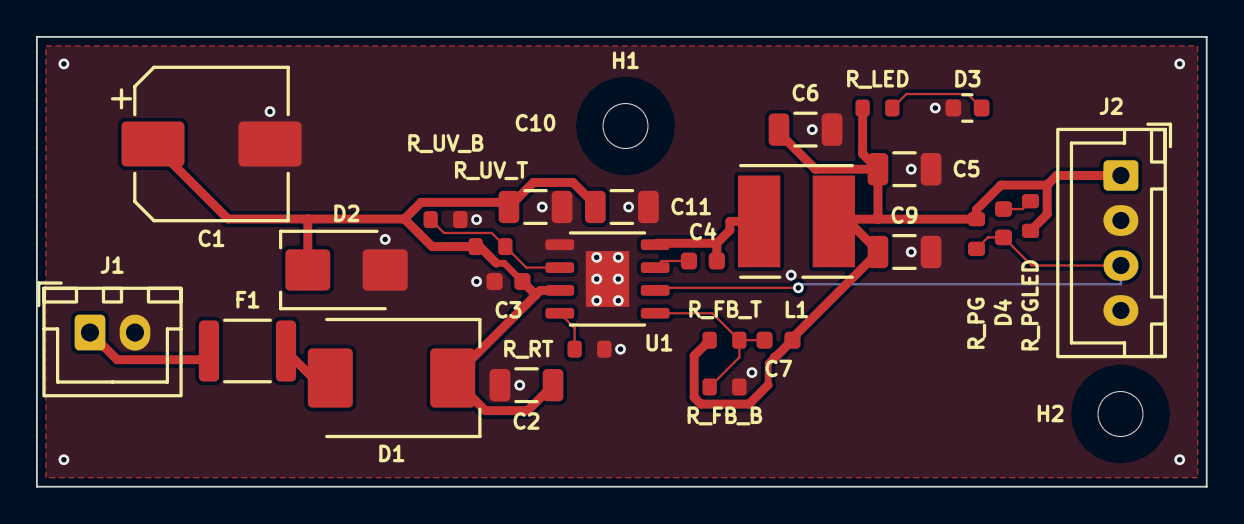
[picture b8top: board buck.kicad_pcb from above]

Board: 4 copper layers, 65.0 x 25.0 mm, 29 parts (0 on the bottom side), 13 nets.

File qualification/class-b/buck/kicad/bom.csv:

refdes,value,kind,description,kicad_symbol,kicad_footprint,lcsc_pn,mpn
C1,47uF,capacitor,"Honor Elec RVT1H470M0810, 47 uF 50 V +/-20 % 105 C SMD aluminium electrolytic, 8 mm diameter x 10.2 mm, polarised (pin 1 is +); JLCPCB C2895739",Device:C_Polarized,Capacitor_SMD:CP_Elec_8x10,,RVT1H470M0810
C10,10uF,capacitor,"Samsung CL31B106KBHNNNE, 10 uF +/-10 % 50 V X7R 1206 MLCC, -55 to 125 C (distributor listing); JLCPCB C89632",Device:C,Capacitor_SMD:C_1206_3216Metric,C89632,CL31B106KBHNNNE
C11,10uF,capacitor,"Samsung CL31B106KBHNNNE, 10 uF +/-10 % 50 V X7R 1206 MLCC, -55 to 125 C (distributor listing); JLCPCB C89632",Device:C,Capacitor_SMD:C_1206_3216Metric,C89632,CL31B106KBHNNNE
C2,10uF,capacitor,"Samsung CL31B106KBHNNNE, 10 uF +/-10 % 50 V X7R 1206 MLCC, -55 to 125 C (distributor listing); JLCPCB C89632",Device:C,Capacitor_SMD:C_1206_3216Metric,C89632,CL31B106KBHNNNE
C3,220nF,capacitor,"Generic 0603 MLCC, X7R/X5R, any value",Device:C,Capacitor_SMD:C_0603_1608Metric,,
C4,100nF,capacitor,"Generic 0603 MLCC, X7R/X5R, any value",Device:C,Capacitor_SMD:C_0603_1608Metric,,
C5,22uF,capacitor,"Samsung CL31A226KAHNNNE, 22 uF +/-10 % 25 V X5R 1206 MLCC, 1.60 mm max thickness, -55 to 85 C, +/-15 % over temperature; JLCPCB C12891",Device:C,Capacitor_SMD:C_1206_3216Metric,C12891,CL31A226KAHNNNE
C6,22uF,capacitor,"Samsung CL31A226KAHNNNE, 22 uF +/-10 % 25 V X5R 1206 MLCC, 1.60 mm max thickness, -55 to 85 C, +/-15 % over temperature; JLCPCB C12891",Device:C,Capacitor_SMD:C_1206_3216Metric,C12891,CL31A226KAHNNNE
C7,56pF,capacitor,"Generic 0603 MLCC, X7R/X5R, any value",Device:C,Capacitor_SMD:C_0603_1608Metric,,
C9,22uF,capacitor,"Samsung CL31A226KAHNNNE, 22 uF +/-10 % 25 V X5R 1206 MLCC, 1.60 mm max thickness, -55 to 85 C, +/-15 % over temperature; JLCPCB C12891",Device:C,Capacitor_SMD:C_1206_3216Metric,C12891,CL31A226KAHNNNE
D1,SS36,diode,"Vishay SS36 60 V 3 A Schottky rectifier, SMC (DO-214AB), for reverse-polarity blocking",Device:D_Schottky,Diode_SMD:D_SMC,,SS36
D2,SMBJ30A,diode,"Vishay SMBJ30A 600 W unidirectional TVS, SMB (DO-214AA). max_voltage_v is the 30 V standoff VWM, not a clamp or abs max: VBR 33.3-36.8 V at 1 mA, VC 48.4 V at 12.4 A",Device:D_Zener,Diode_SMD:D_SMB,,SMBJ30A
D3,PWR,led,"Lite-On LTST-C190KGKT green AlInGaP LED, 0603, Vf 1.9 to 2.4V at 20mA",Device:LED,LED_SMD:LED_0603_1608Metric,,LTST-C190KGKT
D4,PG FAULT,led,"Lite-On LTST-C190KGKT green AlInGaP LED, 0603, Vf 1.9 to 2.4V at 20mA",Device:LED,LED_SMD:LED_0603_1608Metric,,LTST-C190KGKT
F1,1.1A_PTC,fuse,"Bourns MF-MSMF110/33X resettable PTC fuse, 1812. max_current_ma is Ihold 1.1 A at 23 C (0.63 A at 70 C, 0.50 A at 85 C); Itrip 2.2 A, Vmax 33 V",Device:Polyfuse,Fuse:Fuse_1812_4532Metric,,MF-MSMF110/33X
H1,M2.5,mounting_hole,M2.5 non-plated mounting hole (NPTH) for a board corner,Mechanical:MountingHole,MountingHole:MountingHole_2.5mm,,
H2,M2.5,mounting_hole,M2.5 non-plated mounting hole (NPTH) for a board corner,Mechanical:MountingHole,MountingHole:MountingHole_2.5mm,,
J1,24V_IN,connector,"JST XH 2.5 mm pitch 2-pin vertical header B2B-XH-A, 250 V / 3 A per JST XH sheet",Connector_Generic:Conn_01x02,Connector_JST:JST_XH_B2B-XH-A_1x02_P2.50mm_Vertical,,B2B-XH-A
J2,3V3_OUT,connector,"JST XH 2.5 mm pitch 4-pin vertical header B4B-XH-A, 250 V / 3 A per JST XH sheet",Connector_Generic:Conn_01x04,Connector_JST:JST_XH_B4B-XH-A_1x04_P2.50mm_Vertical,,B4B-XH-A
L1,6.8uH,inductor,"Bourns SRN6045TA-6R8M 6.8 uH semi-shielded power inductor, 6.0 x 6.0 mm. Datasheet typ: Isat 5.7 A (L drops 30%), Irms 3.6 A (max_current_ma is Irms), DCR 34 mOhm +-20%",Device:L,Inductor_SMD:L_Bourns_SRN6045TA,,SRN6045TA-6R8M
R_FB_B,43.2k,resistor,"Generic 0603 thick-film resistor, any value",Device:R_US,Resistor_SMD:R_0603_1608Metric,,
R_FB_T,100k,resistor,"Generic 0603 thick-film resistor, any value",Device:R_US,Resistor_SMD:R_0603_1608Metric,,
R_LED,470,resistor,"Generic 0603 thick-film resistor, any value",Device:R_US,Resistor_SMD:R_0603_1608Metric,,
R_PG,100k,resistor,"Generic 0603 thick-film resistor, any value",Device:R_US,Resistor_SMD:R_0603_1608Metric,,
R_PGLED,470,resistor,"Generic 0603 thick-film resistor, any value",Device:R_US,Resistor_SMD:R_0603_1608Metric,,
R_RT,33k,resistor,"Generic 0603 thick-film resistor, any value",Device:R_US,Resistor_SMD:R_0603_1608Metric,,
R_UV_B,100k,resistor,"Generic 0603 thick-film resistor, any value",Device:R_US,Resistor_SMD:R_0603_1608Metric,,
R_UV_T,1.37M,resistor,"Generic 0603 thick-film resistor, any value",Device:R_US,Resistor_SMD:R_0603_1608Metric,,
U1,LMR38010SDDAR,regulator,"TI LMR38010SDDAR 4.2-80 V input, 1 A synchronous step-down converter, adjustable 400 kHz-2.2 MHz through RT, PFM with spread spectrum, HSOIC-8 (DDA) with exposed thermal pad and open-drain power-good. VFB 1.0 V; VIN abs max 85 V",,Package_SO:HSOP-8-1EP_3.9x4.9mm_P1.27mm_EP2.41x3.1mm,,LMR38010SDDAR
